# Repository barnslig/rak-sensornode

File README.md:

# RAK3172 Feather

The RAK3172 feather is a [LoRa](https://www.semtech.com/lora) development board, based on the popular [Adafruit Feather](https://learn.adafruit.com/adafruit-feather/feather-specification) format. It features the [STM32WLE5](https://www.st.com/en/microcontrollers-microprocessors/stm32wle5cc.html) 32-bit ARM Cortex-M4 microcontroller, with 256 Kbytes of Flash memory and 64 Kbytes of SRAM. Being optimized for ultra-low power using the [TPS62840](https://www.ti.com/product/de-de/TPS62840) step-down converter, the board can be used for rapid prototyping of battery-powered IoT sensor nodes.

To ease development, the board is equipped with an on-board [CH343P](https://www.wch-ic.com/products/CH343.html) USB-TTL and a 200mA [TP4054](https://www.umw-ic.com/static/pdf/46c15f53afcf69d99cf4bf3c625c6952.pdf) Li-Po battery charger.

## PCB

## Schematic

## Power

External power:

- Board can be powered via USB.
- Connect 3 - 6V DC to VBUS pin or BAT pin.

Battery:

- Connect battery using the JST PH-2 connector or via BAT pin.
- There is an integrated Li-Ion / Li-Po charger, powered via USB / VBUS pin.
- **Cut the CHG jumper on the backisde to disable the charger when using non-rechargeable batterys, e.g. Li-SoCl2 / Li-MnO2!**

Battery Monitoring:

- The voltage on BAT can be measured using the integrated ADC.
- Pull PA8 to GND.
- Measure voltage on PB3 / A0 using the integrated ADC.
- Calculate the battery voltage as follows: `mV * (4700 + 10000) / 10000`.

## User LED

- Integrated LED is connected to PA0 pin.
- Cut the LED jumper on the backside to use the PA0 pin for something else.

## Programming and Firmware

Factory firmware is RUI3 by RAKwireless. See [RAK3172 WisDuo LPWAN Module](https://docs.rakwireless.com/Product-Categories/WisDuo/RAK3172-Module/Overview/).

- Programming can be done via USB serial.
- For programming and debugging, use SWD via the TC2030 connector.

## License

See [LICENSE](./LICENSE).

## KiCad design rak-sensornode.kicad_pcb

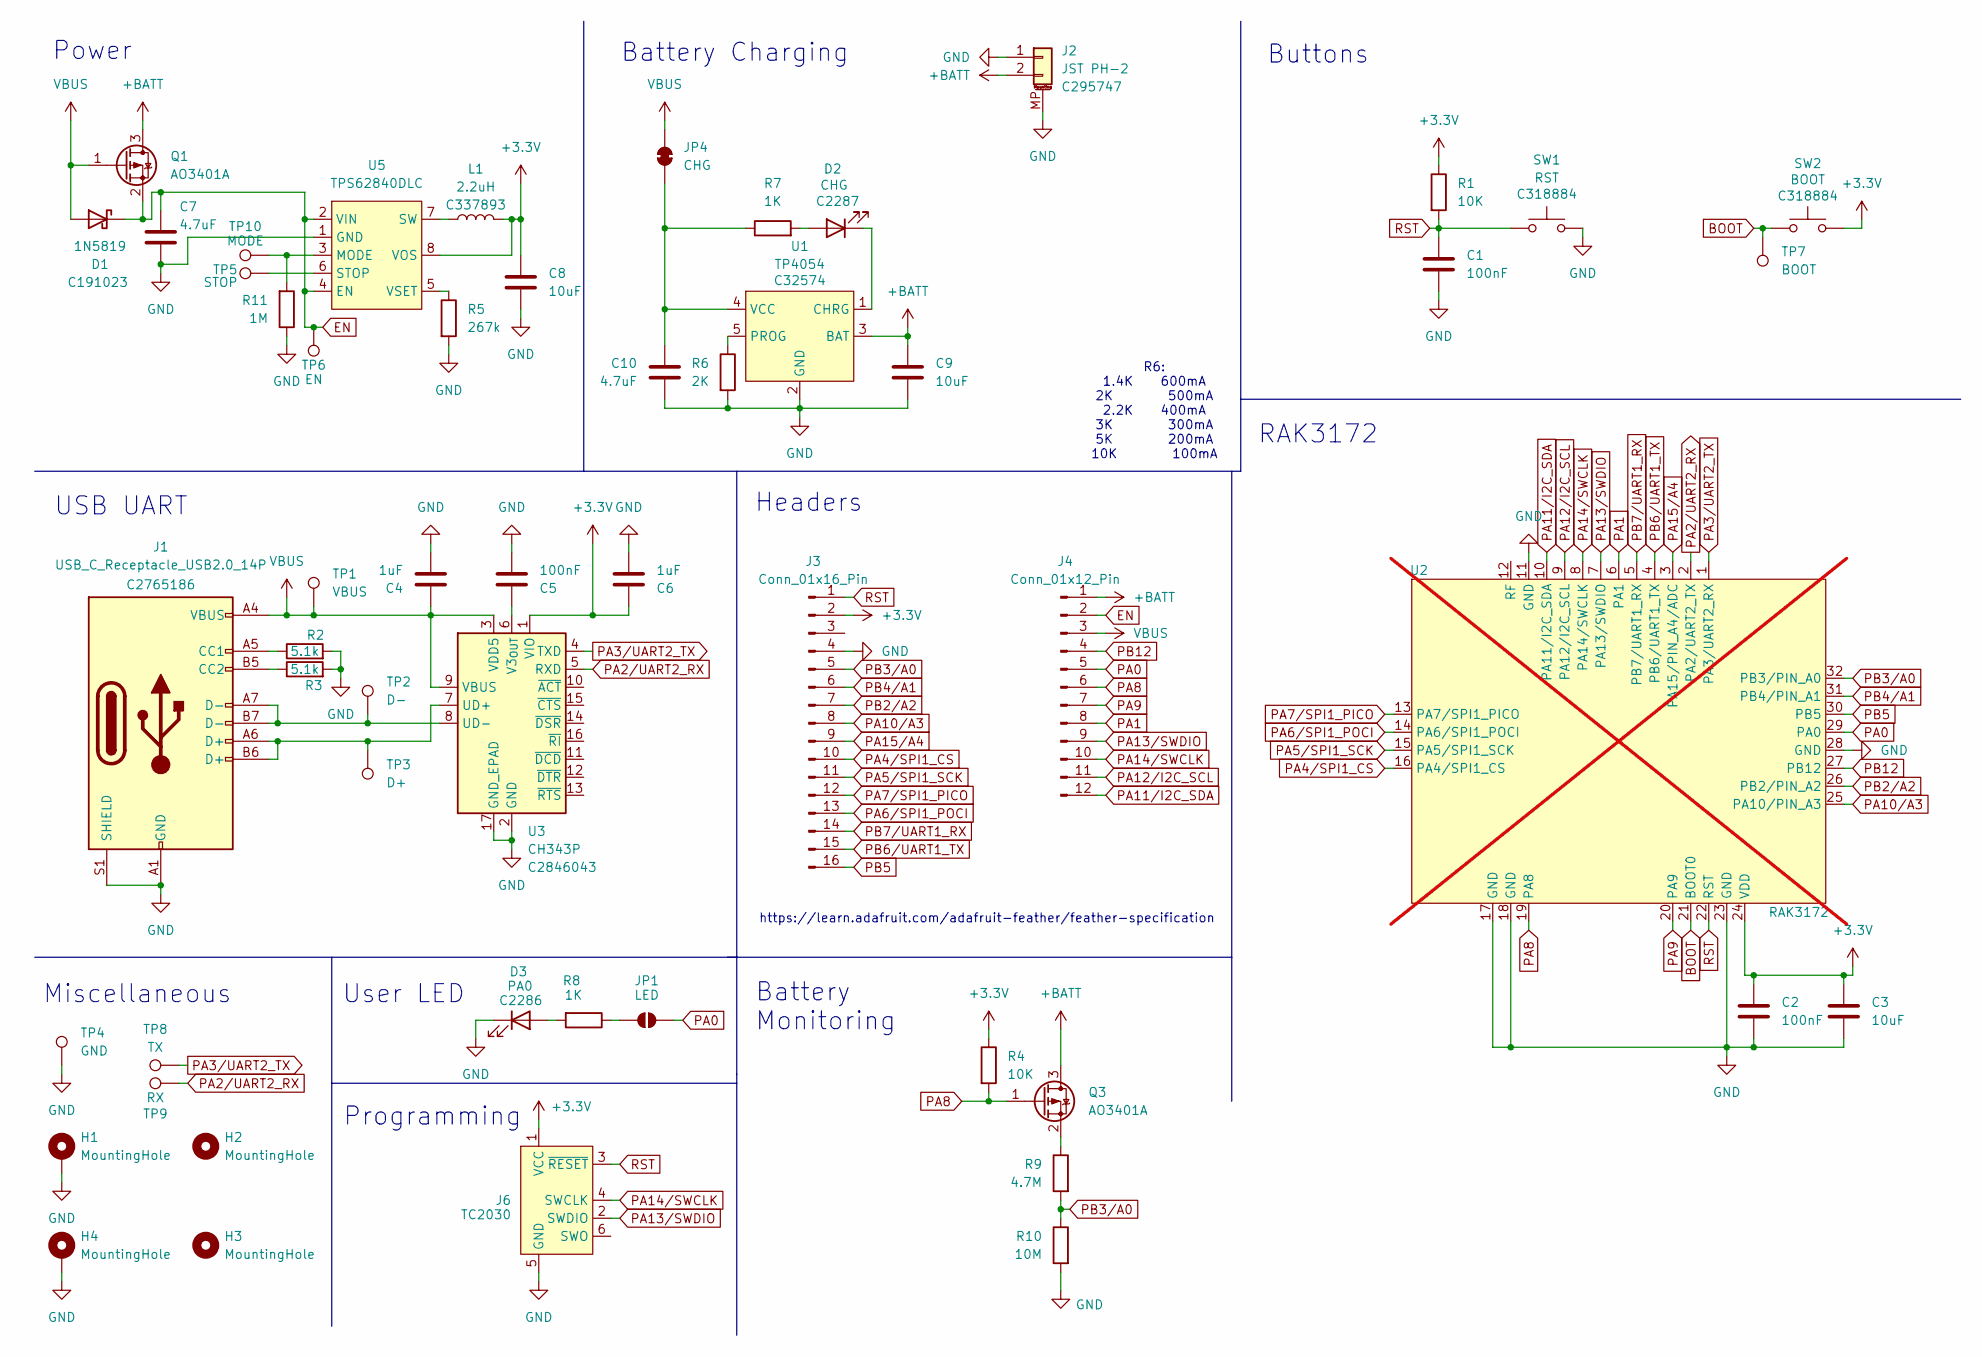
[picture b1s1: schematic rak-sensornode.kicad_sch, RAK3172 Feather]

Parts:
C1, C2, C5: 100nF; C_0402_1005Metric
C3, C8, C9: 10uF; C_0402_1005Metric
C4, C6: 1uF; C_0402_1005Metric
C7, C10: 4.7uF; C_0402_1005Metric
D1: 1N5819; D_SOD-323; LCSC Part # C191023
D2: CHG; LED_0603_1608Metric; LCSC Part # C2287
D3: PA0; LED_0603_1608Metric; LCSC Part # C2286
H1, H4: MountingHole; MountingHole_2.5mm_Pad_TopBottom
H2, H3: MountingHole; MountingHole_2.5mm
J1: USB_C_Receptacle_USB2.0_14P; USB_C_Receptacle_XKB_U262-16XN-4BVC11; LCSC Part # C2765186
J2: JST PH-2; JST_PH_S2B-PH-SM4-TB_1x02-1MP_P2.00mm_Horizontal; LCSC Part # C295747
J3: Conn_01x16_Pin; PinHeader_1x16_P2.54mm_Vertical
J4: Conn_01x12_Pin; PinHeader_1x12_P2.54mm_Vertical
J6: TC2030; Tag-Connect_TC2030-IDC-NL_2x03_P1.27mm_Vertical
JP1: LED; SolderJumper-2_P1.3mm_Bridged_RoundedPad1.0x1.5mm
JP4: CHG; SolderJumper-2_P1.3mm_Bridged_RoundedPad1.0x1.5mm
L1: 2.2uH; L_Murata_DFE201612E; LCSC Part # C337893
Q1, Q3: AO3401A; SOT-23
R1, R4: 10K; R_0402_1005Metric
R2, R3: 5.1k; R_0402_1005Metric
R5: 267k; R_0402_1005Metric
R6: 2K; R_0402_1005Metric
R7, R8: 1K; R_0402_1005Metric
R9: 4.7M; R_0402_1005Metric
R10: 10M; R_0402_1005Metric
R11: 1M; R_0402_1005Metric
SW1: RST; TS-1187A-B-A-B; LCSC Part # C318884
SW2: BOOT; TS-1187A-B-A-B; LCSC Part # C318884
TP1: VBUS; TestPoint_Pad_D1.0mm
TP2: D-; TestPoint_Pad_D1.0mm
TP3: D+; TestPoint_Pad_D1.0mm
TP4: GND; TestPoint_Pad_D1.0mm
TP5: STOP; TestPoint_Pad_D1.0mm
TP6: EN; TestPoint_Pad_D1.0mm
TP7: BOOT; TestPoint_Pad_D1.0mm
TP8: TX; TestPoint_Pad_D1.0mm
TP9: RX; TestPoint_Pad_D1.0mm
TP10: MODE; TestPoint_Pad_D1.0mm
U1: TP4054; SOT-23-5; LCSC Part # C32574
U2: RAK3172; not fitted
U3: CH343P; WCH_QFN-16-1EP_3x3mm_P0.5mm_EP1.8x1.8mm; LCSC Part # C2846043
U5: TPS62840DLC; VSON-8_1.5x2mm_P0.5mm; LCSC Part C2071859

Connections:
+3.3V: C2.1, C3.1, C6.1, C8.1, J3.2, J6.1 (VCC), L1.2, R1.1, R4.1, SW2.2, U2.24 (VDD), U3.1 (VIO), U5.8 (VOS)
+BATT: C9.1, J2.2, J4.1, Q1.3 (D), Q3.3 (D), U1.3 (BAT)
BOOT: SW2.1, TP7.1, U2.21 (BOOT0)
EN: C7.1, D1.1 (K), J4.2, Q1.2 (S), TP6.1, U5.2 (VIN), U5.4 (EN)
GND: C1.2, C2.2, C3.2, C4.2, C5.2, C6.2, C7.2, C8.2, C9.2, C10.2, D3.1 (K), H1.1, H4.1, J1.A1 (GND), J1.A12 (GND), J1.B1 (GND), J1.B12 (GND), J1.S1 (SHIELD), J2.1, J2.MP (MountPin), J3.4, J6.5 (GND), R2.2, R3.2, R5.2, R6.2, R10.2, R11.1, SW1.2, TP4.1, U1.2 (GND), U2.11 (GND), U2.17 (GND), U2.18 (GND), U2.23 (GND), U2.28 (GND), U3.2 (GND), U3.17 (GND_EPAD), U5.1 (GND)
unnamed: D2.2 (A), R7.2
unnamed: D2.1 (K), U1.1 (CHRG)
unnamed: D3.2 (A), R8.2
unnamed: J1.A5 (CC1), R2.1
unnamed: J1.B5 (CC2), R3.1
unnamed: JP1.1 (A), R8.1
unnamed: C10.1, JP4.1 (A), R7.1, U1.4 (VCC)
unnamed: Q3.2 (S), R9.1
unnamed: R6.1, U1.5 (PROG)
unnamed: J1.A6 (D+), J1.B6 (D+), TP3.1, U3.7 (UD+)
unnamed: J1.A7 (D-), J1.B7 (D-), TP2.1, U3.8 (UD-)
unnamed: C5.1, U3.6 (V3_{OUT})
unnamed: R11.2, TP10.1, U5.3 (MODE)
unnamed: TP5.1, U5.6 (STOP)
unnamed: L1.1, U5.7 (SW)
unnamed: R5.1, U5.5 (VSET)
PA0: J4.5, JP1.2 (B), U2.29 (PA0)
PA1: J4.8, U2.6 (PA1)
PA2/UART2_RX: TP9.1, U2.2 (PA2/UART2_TX), U3.5 (RXD)
PA3/UART2_TX: TP8.1, U2.1 (PA3/UART2_RX), U3.4 (TXD)
PA4/SPI1_CS: J3.10, U2.16 (PA4/SPI1_CS)
PA5/SPI1_SCK: J3.11, U2.15 (PA5/SPI1_SCK)
PA6/SPI1_POCI: J3.13, U2.14 (PA6/SPI1_POCI)
PA7/SPI1_PICO: J3.12, U2.13 (PA7/SPI1_PICO)
PA8: J4.6, Q3.1 (G), R4.2, U2.19 (PA8)
PA9: J4.7, U2.20 (PA9)
PA10/A3: J3.8, U2.25 (PA10/PIN_A3)
PA11/I2C_SDA: J4.12, U2.10 (PA11/I2C_SDA)
PA12/I2C_SCL: J4.11, U2.9 (PA12/I2C_SCL)
PA13/SWDIO: J4.9, J6.2 (SWDIO), U2.7 (PA13/SWDIO)
PA14/SWCLK: J4.10, J6.4 (SWCLK), U2.8 (PA14/SWCLK)
PA15/A4: J3.9, U2.3 (PA15/PIN_A4/ADC)
PB2/A2: J3.7, U2.26 (PB2/PIN_A2)
PB3/A0: J3.5, R9.2, R10.1, U2.32 (PB3/PIN_A0)
PB4/A1: J3.6, U2.31 (PB4/PIN_A1)
PB5: J3.16, U2.30 (PB5)
PB6/UART1_TX: J3.15, U2.4 (PB6/UART1_TX)
PB7/UART1_RX: J3.14, U2.5 (PB7/UART1_RX)
PB12: J4.4, U2.27 (PB12)
RST: C1.1, J3.1, J6.3 (~RESET), R1.2, SW1.1, U2.22 (RST)
VBUS: C4.1, D1.2 (A), J1.A4 (VBUS), J1.A9 (VBUS), J1.B4 (VBUS), J1.B9 (VBUS), J4.3, JP4.2 (B), Q1.1 (G), TP1.1, U3.3 (VDD5), U3.9 (VBUS)

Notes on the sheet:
USB UART
Miscellaneous
RAK3172
Power
Buttons
R6: 1.4K 600mA 2K 500mA 2.2K 400mA 3K 300mA 5K 200mA 10K 100mA
Headers
User LED
https://learn.adafruit.com/adafruit-feather/feather-specification
Battery Charging
Programming
Battery Monitoring

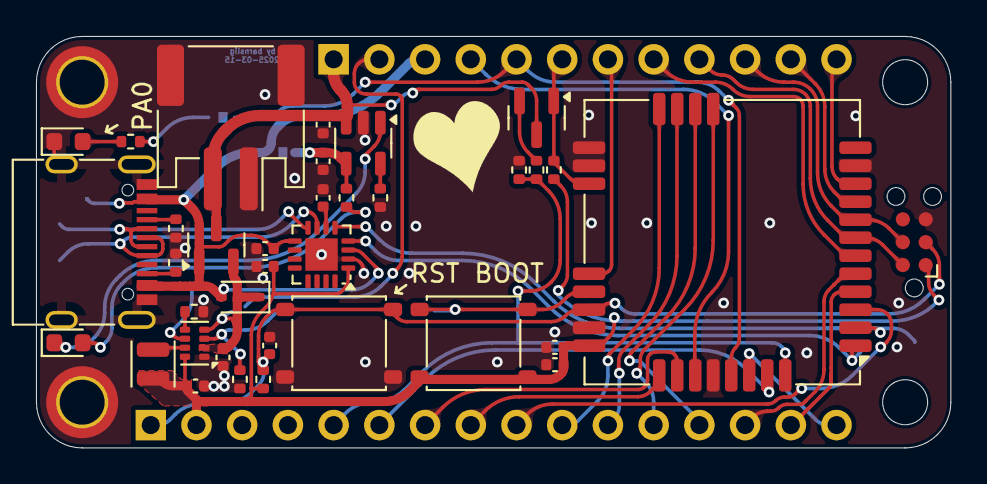
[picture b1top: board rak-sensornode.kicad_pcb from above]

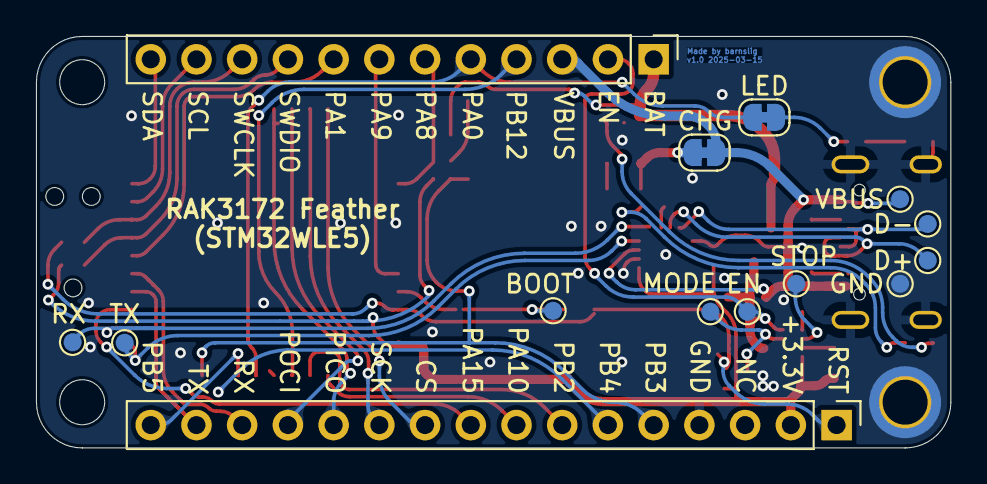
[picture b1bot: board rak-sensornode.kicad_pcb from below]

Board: 2 copper layers, 50.8 x 22.9 mm, 54 parts (14 on the bottom side), 46 nets.

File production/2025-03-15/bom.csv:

Designator,Footprint,Quantity,Value,LCSC Part #
"C1, C2, C5",0402,3,100nF,
"C10, C7",0402,2,4.7uF,
"C3, C8, C9",0402,3,10uF,
"C4, C6",0402,2,1uF,
D1,D_SOD-323,1,1N5819,C191023
D2,0603,1,CHG,C2287 
D3,0603,1,PA0,C2286
J1,USB_C_Receptacle_XKB_U262-16XN-4BVC11,1,USB_C_Receptacle_USB2.0_14P,C2765186
J2,JST_PH_S2B-PH-SM4-TB_1x02-1MP_P2.00mm_Horizontal,1,JST PH-2,C295747
L1,L_Murata_DFE201612E,1,2.2uH,C337893
Q1,SOT-23,1,AO3401A,
Q3,SOT-23,1,AO3401A,
R1,0402,1,10K,
R10,0402,1,10M,
R11,0402,1,1M,
"R2, R3",0402,2,5.1k,
R4,0402,1,10K,
R5,0402,1,267k,
R6,0402,1,2K,
"R7, R8",0402,2,1K,
R9,0402,1,4.7M,
SW1,TS-1187A-B-A-B,1,RST,C318884
SW2,TS-1187A-B-A-B,1,BOOT,C318884
U1,SOT-23-5,1,TP4054,C32574
U3,WCH_QFN-16-1EP_3x3mm_P0.5mm_EP1.8x1.8mm,1,CH343P,C2846043
U5,VSON-8_1.5x2mm_P0.5mm,1,TPS62840DLC,C2071859

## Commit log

2025-03-22 feat: Initial commit
